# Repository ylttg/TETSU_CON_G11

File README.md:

# TETSU_CON_G11
Small rail load model controller using RL78/G11

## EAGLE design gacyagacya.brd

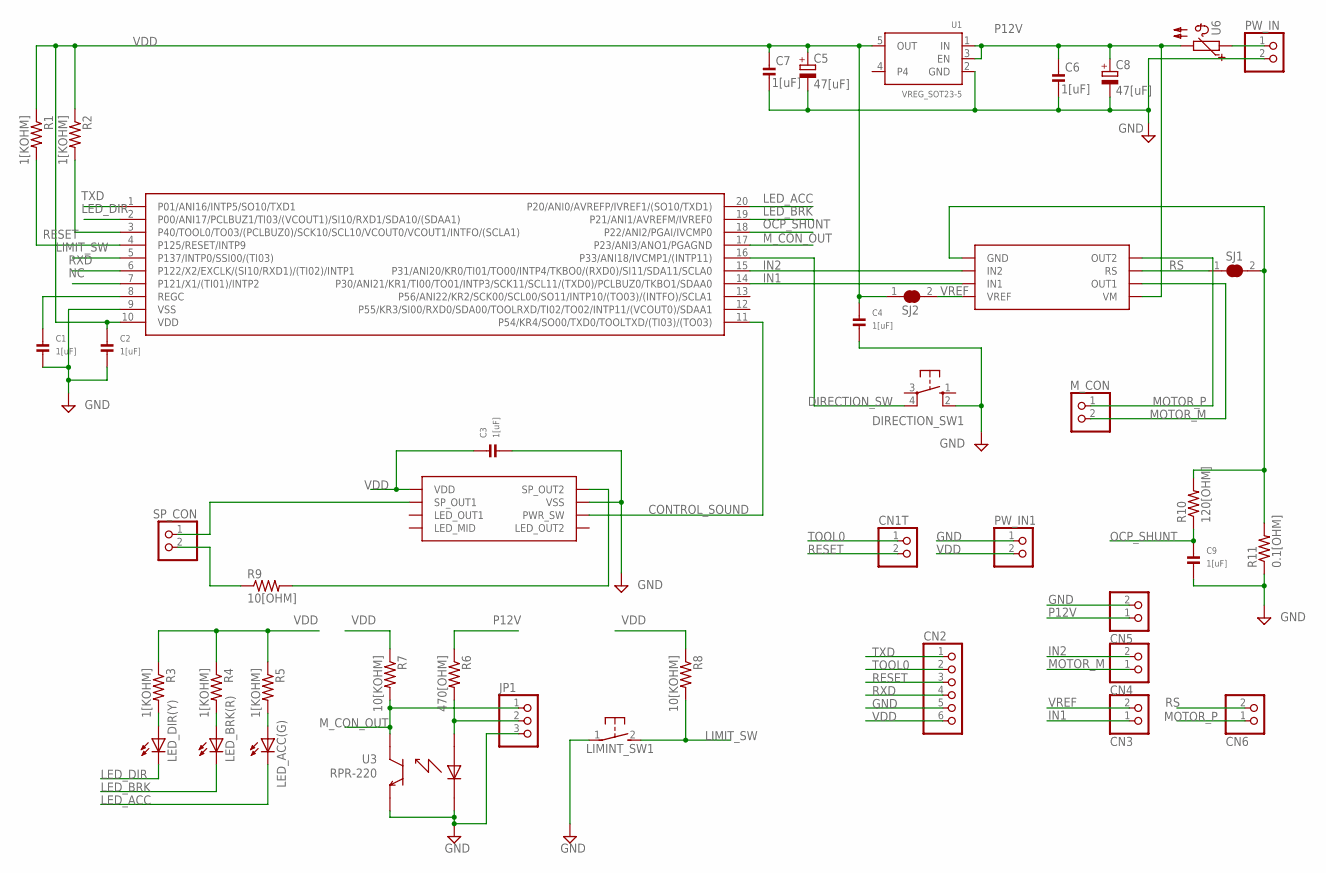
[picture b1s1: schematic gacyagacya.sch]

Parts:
C1, C2, C3, C4, C6, C7, C9: 1[uF]; _0603
C5, C8: 47[uF]; E1,8-4
CN1T, CN3, CN4, CN5, CN6: HEADER-1X2ROUND; 1X02_ROUND
CN2: XSR_6PIN
DIRECTION_SW1: 10-XXSMD_TACT_SW; SMD_TACT_SW
JP1: HEADER-1X3ROUND; 1X03_ROUND
LED_ACC(G): LED3MM
LED_BRK(R): LED3MM
LED_DIR(Y): LED3MM
LIMINT_SW1: 31-XX; B3F-31XX
M_CON: HEADER-1X2ROUND; 1X02_ROUND
PW_IN, PW_IN1: HEADER-1X2ROUND; 1X02_ROUND
R1, R2, R3, R4, R5: 1[KOHM]; R0603
R6: 470[OHM]; R0603
R7, R8: 10[KOHM]; R0603
R9: 10[OHM]; R0603
R10: 120[OHM]; R0603
R11: 0.1[OHM]; R0603
SJ1, SJ2: SOLDERJUMPER_CLOSEDPERM
SP_CON: HEADER-1X2ROUND; 1X02_ROUND
U1: VREG_SOT23-5; SOT23-5
U2: RL78/G11_SSOP20; SSOP20_225MIL
U3: RPR-220; RPR-220_FOOT_PRINT
U4: TB67H450FNG; SOP8
U5: SOUND_IC_FOR_TETSUKON_GACYA
U6: RESETTABLE-PTC-5MM; DIP_5MM

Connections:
CONTROL_SOUND: U2.11 (P54/KR4/SO00/TXD0/TOOLTXD/(TI03)/(TO03)), U5.6 (PWR_SW)
DIRECTION_SW: DIRECTION_SW1.4 (P1), U2.16 (P33/ANI18/IVCMP1/(INTP11))
DRIVEROUT: R10.2, R11.2, SJ1.2, U4.1 (GND)
GND: C1.2, C2.2, C3.2, C4.2, C5.-, C6.2, C7.2, C8.-, C9.2, CN2.5, CN5.2, DIRECTION_SW1.2 (S1), JP1.3, LIMINT_SW1.1, PW_IN.2, PW_IN1.1, R11.1, U1.2 (GND), U2.9 (VSS), U3.P$2, U3.P$3, U5.7 (VSS)
IN1: CN3.1, U2.14 (P30/ANI21/KR1/TI00/TO01/INTP3/SCK11/SCL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), U4.3 (IN1)
IN2: CN4.2, U2.15 (P31/ANI20/KR0/TI01/TO00/INTP4/TKBO0/(RX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), U4.2 (IN2)
LED_ACC: LED_ACC(G).K (C), U2.20 (P20/ANI0/AVREFP/IVREF1/(SO10/TXD1))
LED_BRK: LED_BRK(R).K (C), U2.19 (P21/ANI1/AVREFM/IVREF0)
LED_DIR: LED_DIR(Y).K (C), U2.2 (P00/ANI17/PCLBUZ1/TI03/(VCOUT1)/SI10/RX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)
LIMIT_SW: LIMINT_SW1.2 (S), R8.2, U2.5 (P137/INTP0/SSI00/(TI03))
MOTOR_M: CN4.1, M_CON.2, U4.6 (OUT1)
MOTOR_P: CN6.1, M_CON.1, U4.8 (OUT2)
M_CON_OUT: JP1.1, R7.2, U2.17 (P23/ANI3/ANO1/PGAGND), U3.P$4
unnamed: LED_DIR(Y).A, R3.2
unnamed: PW_IN.1, U6.1
unnamed: LED_ACC(G).A, R5.2
unnamed: C1.1, U2.8 (REGC)
unnamed: R9.2, U5.8 (SP_OUT2)
unnamed: R9.1, SP_CON.2
unnamed: LED_BRK(R).A, R4.2
unnamed: JP1.2, R6.2, U3.P$1
unnamed: SP_CON.1, U5.2 (SP_OUT1)
NC: U2.7 (P121/X1/(TI01)/INTP2)
OCP_SHUNT: C9.1, R10.1, U2.18 (P22/ANI2/PGAI/IVCMP0)
P12V: C6.1, C8.+, CN5.1, R6.1, U1.1 (IN), U1.3 (EN), U4.5 (VM), U6.2
RESET: CN1T.2, CN2.3, R1.2, U2.4 (P125/RESET/INTP9)
RS: CN6.2, SJ1.1, U4.7 (RS)
RXD: CN2.4, U2.6 (P122/X2/EXCLK/(SI10/RXD1)/(TI02)/INTP1)
TOOL0: CN1T.1, CN2.2, R2.2, U2.3 (P40/TOOL0/TO03/(PCLBUZ0)/SCK10/SCL10/VC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)
TXD: CN2.1, U2.1 (P01/ANI16/INTP5/SO10/TXD1)
VDD: C2.1, C3.1, C4.1, C5.+, C7.1, CN2.6, PW_IN1.2, R1.1, R2.1, R3.1, R4.1, R5.1, R7.1, R8.1, SJ2.1, U1.5 (OUT), U2.10 (VDD), U5.1 (VDD)
VREF: CN3.2, SJ2.2, U4.4 (VREF)

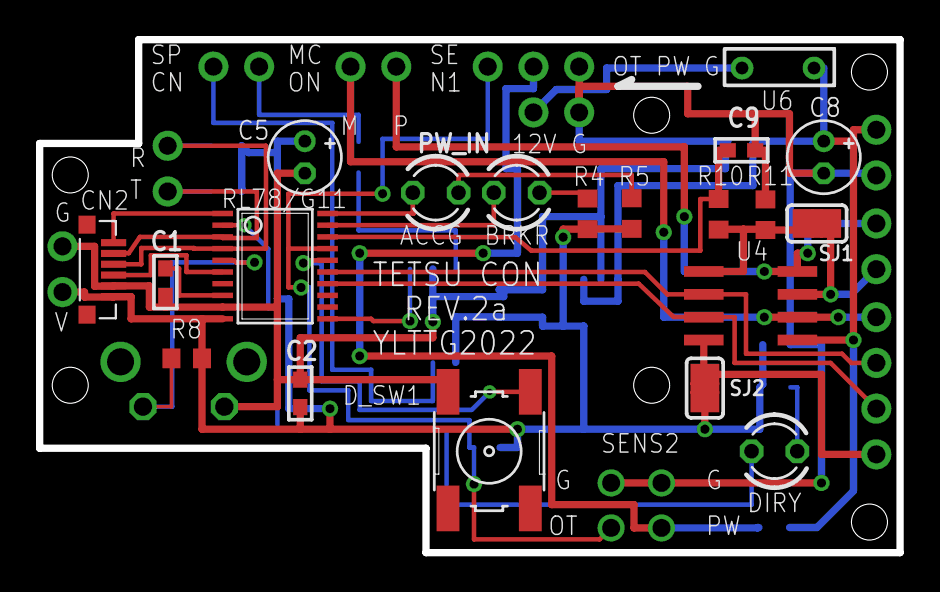
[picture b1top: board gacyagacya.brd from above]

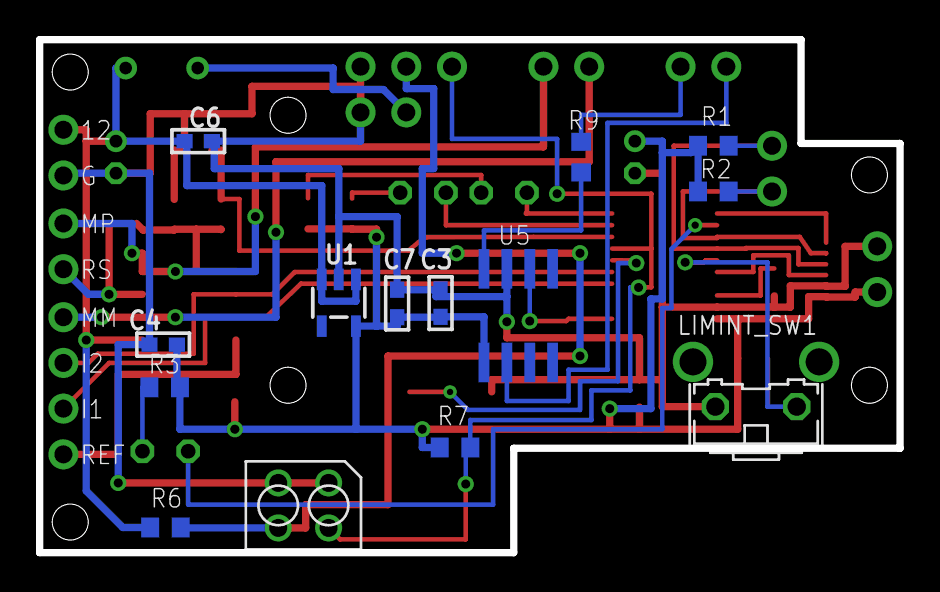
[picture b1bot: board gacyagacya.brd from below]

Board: 2 copper layers, 47.8 x 28.5 mm, 44 parts (14 on the bottom side), 31 nets.

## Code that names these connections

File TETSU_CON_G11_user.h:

#include <iodefine.h>
#include 	"r_cg_macrodriver.h"
#include 	"r_cg_cgc.h"
#include 	"r_cg_port.h"
#include 	"r_cg_tau.h"
#include 	"r_cg_it8bit.h"
#include 	"r_cg_tmkb.h"
#include 	"r_cg_wdt.h"
#include 	"r_cg_sau.h"
#include 	"r_cg_adc.h"
#include	"r_cg_dac.h"
#include 	"r_cg_pga.h"
#include 	"r_cg_comp.h"

/* port definision */
#define	LED_ACC_PORT		P2_bit.no0		/* rev2 */
#define LED_BRK_PORT		P2_bit.no1		/* rev2 */
#define LED_ACC			0
#define LED_BRK			1
#define LED_DIRECTION		2
#define IN2_PORT		P3_bit.no1
#define IN1_PORT		P3_bit.no0
#define STBY_PORT		P5_bit.no5
#define CONTROL_SOUND		P5_bit.no4
#define PWMA_PORT		P5_bit.no6
#define ADCH_M_CON_OUT		3			/* ANI3 */
#define ADCH_OCP_SHUNT		2			/* ANI2 */	
#define LED_DIRECTION_PORT	P0_bit.no0		/* rev2 */
#define LIMIT_SW_PORT		P13_bit.no7
#define DIRECTION_SW_PORT	P3_bit.no3
#define DIRECTION_DEFAULT	1
#define	LED_ON			0
#define LED_OFF			1
#define SW_ON			0
#define SW_OFF			1
#define SOUND_ON		1
#define SOUND_OFF		0
#define SOUND_LIMIT		100			/* 1ms * 100 = 100ms */
#define INTERVAL_COUNT		100			/* 1ms * 100 = 100ms */
#define SW_CHATTERING_COUNT 	50			/* 1ms * 50 = 50ms */
#define STEP_COUNT 		16
#define BLINK_ON		1
#define BLINK_OFF		0
#define BLINK_FAST		2
#define BLINK_PERIOD		500			/* 1ms * 500 = 500ms */
#define BLINK_PERIOD_FAST	100
#define EM_OFF			0
#define EM_ALART		1
#define LIGHT_ON		1
#define LIGHT_OFF		0
#define SPEED_LIMIT_PERCENT	100.0			/* 100% */
#define JUMP_START_PERCENT	20.0			/* 20% */
#define ALLWAYS_LIGHT_ON_PERCENT 10.0			/* 10% */

/* for rev2 */
#define SPEED_LIMIT_VALUE	((unsigned int )( _01DF_TMKB_CYCLE00_VALUE * SPEED_LIMIT_PERCENT / 100.0 ))
#define JUMP_START_VALUE	((unsigned int )( _01DF_TMKB_CYCLE00_VALUE * JUMP_START_PERCENT / 100.0 ))
#define ALLWAYS_LIGHT_ON_VALUE  ((unsigned int )( _01DF_TMKB_CYCLE00_VALUE * ALLWAYS_LIGHT_ON_PERCENT / 100.0 ))


#define wait10us()		{wait1us(); wait1us(); wait1us(); wait1us(); wait1us(); wait1us(); wait1us(); wait1us(); wait1us(); wait1us();}
#define wait100us()		{wait10us(); wait10us(); wait10us(); wait10us(); wait10us(); wait10us(); wait10us(); wait10us(); wait10us(); wait10us();}


/* function definision */
void	tetsu_con_g11_main ( void );
void	wait1us( void );
void	advalue_get( unsigned int * , unsigned int * );
void	handle_step_set ( unsigned int * );
int	speed_set ( int , unsigned char  );
void	tmkb_set( int, unsigned char );
unsigned int	tmkb_value_get ( unsigned char );


/* structure definision */
struct led_param {
	unsigned int	blink_count;
	unsigned char	dimlevel;
	unsigned char	blink_flag:2;
	unsigned char	on_off:1;
	unsigned char	blinking:1;
};

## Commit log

2023-01-14 Add files via upload
    first released ver. for V2 board
2023-01-14 Add files via upload
    Added Eagle schematic and board file

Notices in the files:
parts and their libraries:
microbuilder: This work is placed in the public domain, and may be freely used for commercial and non-commercial work with the following conditions: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
